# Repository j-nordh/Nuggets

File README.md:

# Nuggets
Programs filling a need you probably didn't know you felt. But when you do, they're here,

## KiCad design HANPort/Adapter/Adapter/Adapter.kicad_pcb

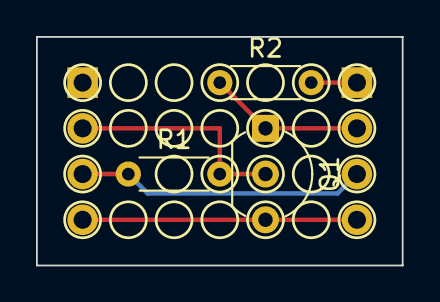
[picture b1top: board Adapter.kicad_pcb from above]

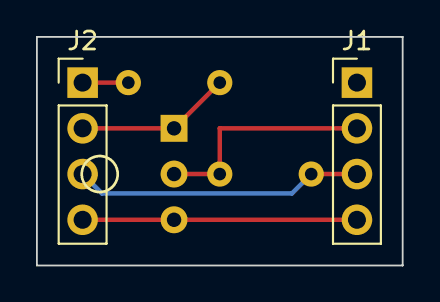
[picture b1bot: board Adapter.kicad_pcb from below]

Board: 2 copper layers, 20.3 x 12.7 mm, 5 parts (2 on the bottom side), 5 nets.

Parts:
J1, J2: Conn_01x04; PinHeader_1x04_P2.54mm_Vertical
Q1: BC337; TO-92_Inline_Wide
R1: 4k7; R_Axial_DIN0204_L3.6mm_D1.6mm_P5.08mm_Horizontal
R2: 10K; R_Axial_DIN0204_L3.6mm_D1.6mm_P5.08mm_Horizontal

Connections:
+3V3: J2.1, R2.2
+5V: J1.3, J2.3, R1.1
/RX: J1.2, Q1.2 (B), R1.2
/TX: J2.2, Q1.1 (C), R2.1
GND: J1.4, J2.4, Q1.3 (E)

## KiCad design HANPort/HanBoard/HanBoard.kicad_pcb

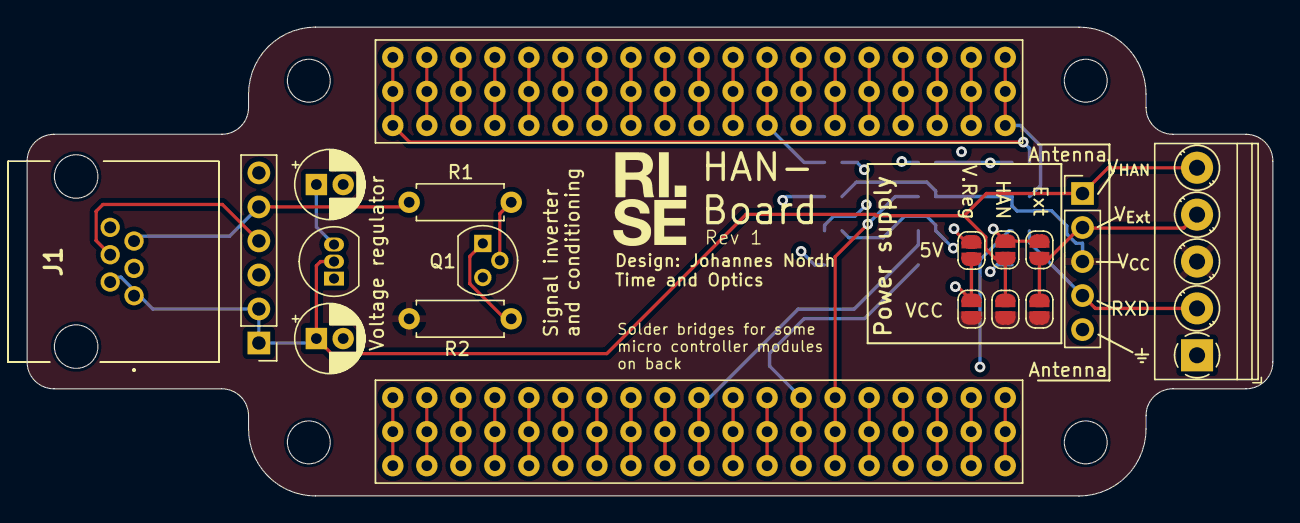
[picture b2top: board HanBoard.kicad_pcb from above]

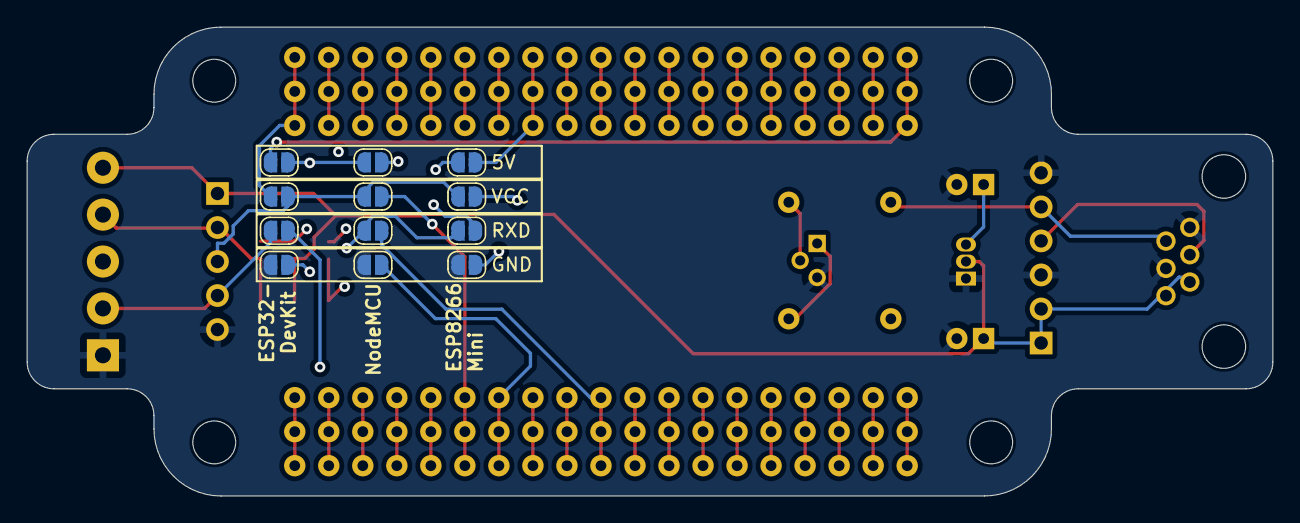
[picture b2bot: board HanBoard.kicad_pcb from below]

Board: 4 copper layers, 93.0 x 35.0 mm, 30 parts (12 on the bottom side), 18 nets.

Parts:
C1, C2: 1 uF; CP_Radial_D5.0mm_P2.00mm
J1: RJ12; RJHSE7060
J2: Conn_01x05; PinHeader_1x05_P2.54mm_Vertical
J3, J5: Lödpunkter; QIP-19
J4: Conn_01x05; PinHeader_1x06_P2.54mm_Vertical
J6: Utterminal; TerminalBlock_Phoenix_PT-1,5-5-3.5-H_1x05_P3.50mm_Horizontal
JP1, JP2, JP3, JP4, JP5, JP6, JP7, JP8, JP9, JP10, JP11, JP12, JP13, JP14, JP15, JP16, JP17, JP18: SolderJumper_2_Open; SolderJumper-2_P1.3mm_Open_RoundedPad1.0x1.5mm
Q1: Q_NPN_BCE; TO-92
R1, R2: R; R_Axial_DIN0207_L6.3mm_D2.5mm_P7.62mm_Horizontal
U1: MCP1700x-330xxTO; TO-92_Inline

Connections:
+5V: JP2.2 (B), JP8.2 (B), JP9.2 (B), JP11.2 (B), JP14.1 (A), JP17.2 (B)
/RXD: J2.4, J6.2, JP1.1 (A), JP12.2 (B), JP15.1 (A), Q1.1 (C), R2.1
GND: C1.2, C2.2, J1.3, J1.6, J2.5, J4.3, J4.6, J6.1, JP4.2 (B), JP10.1 (A), JP16.2 (B), Q1.3 (E), U1.1 (GND)
unnamed: J2.2, J6.4, JP6.1 (A), JP8.1 (A)
unnamed: J3.10, JP1.2 (B)
unnamed: J3.12, JP18.2 (B)
unnamed: J1.4, J4.4
unnamed: J1.5, J4.5, R1.1
unnamed: J5.1, JP2.1 (A)
unnamed: J5.5, JP11.1 (A)
unnamed: J5.6, JP10.2 (B)
unnamed: J5.12, JP17.1 (A)
unnamed: J5.13, JP16.1 (A)
unnamed: J5.18, JP15.2 (B)
unnamed: C2.1, JP13.2 (B), JP14.2 (B), U1.3 (VO)
unnamed: Q1.2 (B), R1.2
VBUS: C1.1, J1.1, J1.2, J2.1, J4.1, J4.2, J6.5, JP7.1 (A), JP9.1 (A), U1.2 (VI)
VCC: J2.3, J6.3, JP3.2 (B), JP5.2 (B), JP6.2 (B), JP7.2 (B), JP13.1 (A), JP18.1 (A), R2.2

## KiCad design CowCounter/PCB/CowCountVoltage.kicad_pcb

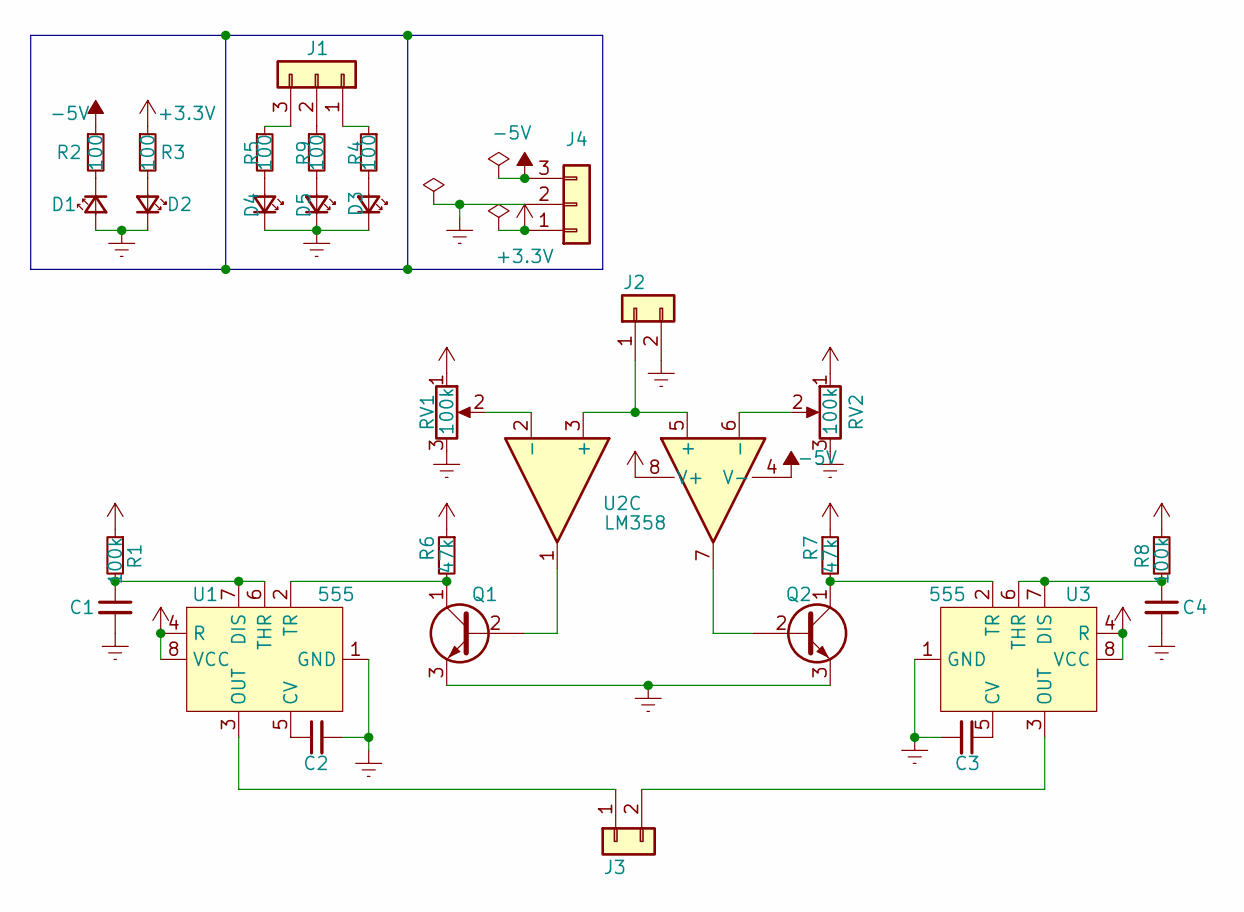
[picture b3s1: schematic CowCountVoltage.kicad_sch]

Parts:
C1, C4: 1uF; C_Disc_D4.3mm_W1.9mm_P5.00mm
C2, C3: 10nF; C_Disc_D4.3mm_W1.9mm_P5.00mm
D1, D2: LED; LED_D3.0mm
D3, D4, D5: LED; LED_D5.0mm
J1: CONN_2; TerminalBlock_MetzConnect_Type101_RT01603HBWC_1x03_P5.08mm_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
J2, J3: CONN_2; TerminalBlock_MetzConnect_Type101_RT01602HBWC_1x02_P5.08mm_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
J4: Conn_01x03; TerminalBlock_MetzConnect_Type101_RT01603HBWC_1x03_P5.08mm_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
Q1, Q2: Q_NPN_CBE; TO-92S_Wide
R1, R8: 100k; R_Axial_DIN0204_L3.6mm_D1.6mm_P5.08mm_Horizontal
R2, R3, R4, R5, R9: 100; R_Axial_DIN0204_L3.6mm_D1.6mm_P5.08mm_Horizontal
R6, R7: 47k; R_Axial_DIN0204_L3.6mm_D1.6mm_P5.08mm_Horizontal
RV1, RV2: 100k; Potentiometer_Vishay_T73XW_Horizontal
U1, U3: 555; DIP-8_W7.62mm
U2: LM358; DIP-8_W7.62mm

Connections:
+3.3V: J4.1, R1.1, R3.1, R6.1, R7.1, R8.1, RV1.1, RV2.1, U1.4 (R), U1.8 (VCC), U2.8 (V+), U3.4 (R), U3.8 (VCC)
-5V: J4.3, R2.1, U2.4 (V-)
Earth: C1.2, C2.2, C3.2, C4.2, D1.2 (A), D2.1 (K), D3.1 (K), D4.1 (K), D5.1 (K), J2.2, J4.2, Q1.3 (E), Q2.3 (E), RV1.3, RV2.3, U1.1 (GND), U3.1 (GND)
unnamed: C1.1, R1.2, U1.6 (THR), U1.7 (DIS)
unnamed: C2.1, U1.5 (CV)
unnamed: C3.1, U3.5 (CV)
unnamed: C4.1, R8.2, U3.6 (THR), U3.7 (DIS)
unnamed: D1.1 (K), R2.2
unnamed: D2.2 (A), R3.2
unnamed: D3.2 (A), R4.2
unnamed: D4.2 (A), R5.2
unnamed: D5.2 (A), R9.2
unnamed: J1.1, R4.1
unnamed: J1.2, R9.1
unnamed: J1.3, R5.1
unnamed: J2.1, U2.3 (+), U2.5 (+)
unnamed: J3.1, U1.3 (OUT)
unnamed: Q1.1 (C), R6.2, U1.2 (TR)
unnamed: Q1.2 (B), U2.1
unnamed: Q2.1 (C), R7.2, U3.2 (TR)
unnamed: Q2.2 (B), U2.7
unnamed: RV1.2, U2.2 (-)
unnamed: RV2.2, U2.6 (-)
unnamed: J3.2, U3.3 (OUT)

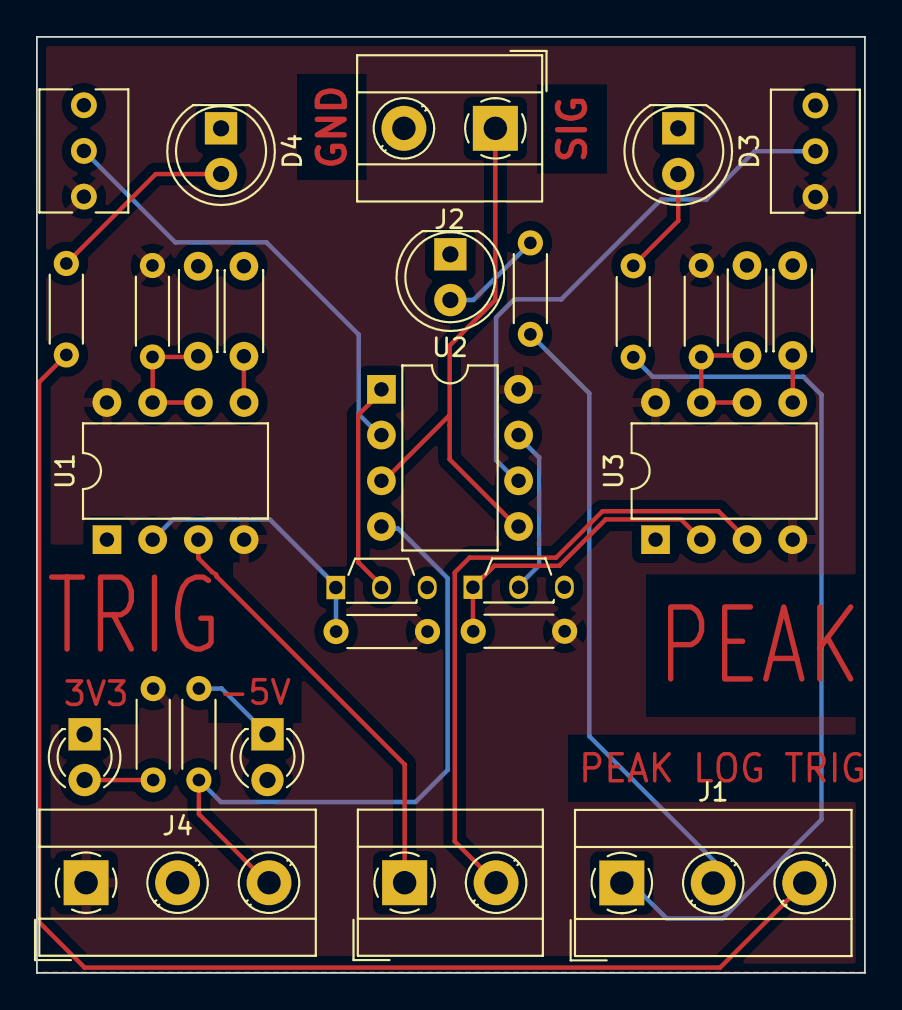
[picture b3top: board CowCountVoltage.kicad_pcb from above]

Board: 2 copper layers, 46.0 x 52.0 mm, 29 parts (0 on the bottom side), 24 nets.

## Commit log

2024-02-20 Extended .gitignore
2024-02-20 Initial commit of all existing Nuggets
2024-02-21 Now it compiles
2024-02-21 Remove starnge file
2024-02-21 Removed strange file
2024-02-21 Cleaning time
